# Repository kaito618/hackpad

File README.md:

# my own macropad (kpad)
### 3x3 macropad with an oled screen

this project is a macropad i designed to fill my needs using my pc what it has :

- 3x3 MX switches (programmable)
- oled screen
- 3d case (optional)
- firmaware

## the schematics

- using the xiao rp2040 as our microcontroller
- connecting the switches directly using "single pin method"
- using i2c with the oled screen 

## PCB design 

## 3d case 

bom
-
| Reference | Component | Footprint | Qty | Description | price | link |
|---|---|---|---|---|---|---|
| U1 | Seeed XIAO RP2040 | XIAO-RP2040-DIP | 1 | Main Microcontroller (MCU) | 
| SW1-SW9 | MX Switches | SW_Cherry_MX_1.00u_PCB | 9 | 1.00u Mechanical switches |
| J1 | 0.91" OLED Display | PinHeader_1x04_P2.54mm | 1 | 128x32 I2C OLED Screen |
| J2 | pcb | pcb | 1 | the board (alr bought) |
| J3 | 3d case | case | 1 | the case (alr bought) |

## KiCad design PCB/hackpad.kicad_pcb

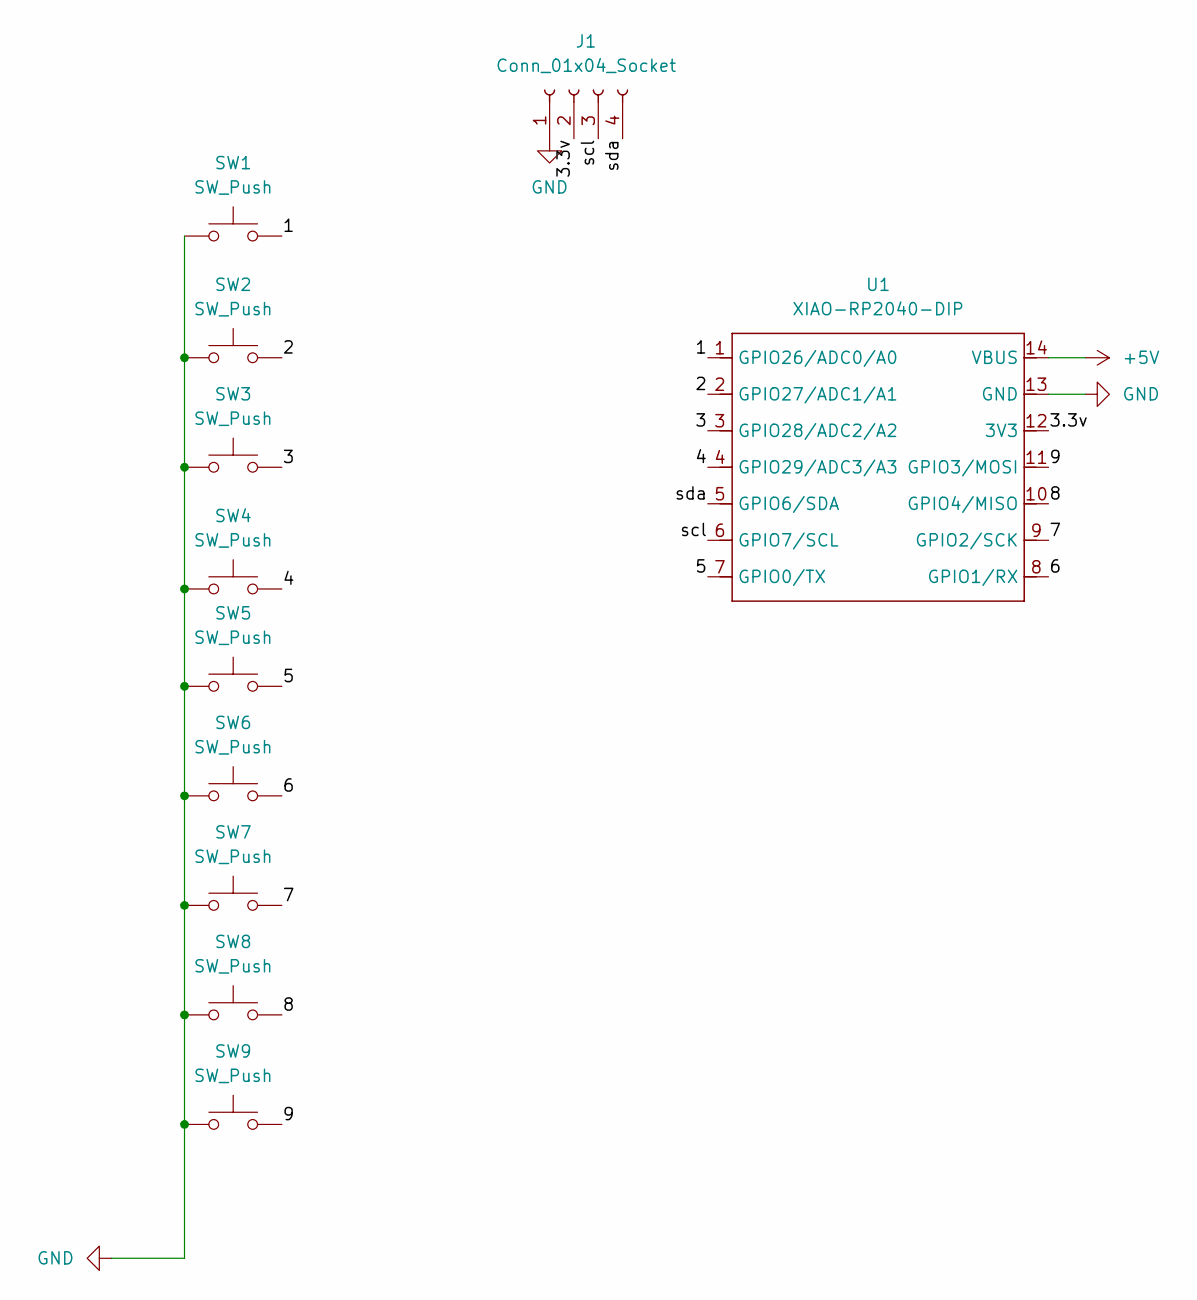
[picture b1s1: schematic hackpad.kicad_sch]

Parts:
J1: Conn_01x04_Socket; PinHeader_1x04_P2.54mm_Vertical
SW1, SW2, SW3, SW4, SW5, SW6, SW7, SW8, SW9: SW_Push; SW_Cherry_MX_1.00u_PCB
U1: XIAO-RP2040-DIP

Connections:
+5V: U1.14 (VBUS)
/1: SW1.2, U1.1 (GPIO26/ADC0/A0)
/2: SW2.2, U1.2 (GPIO27/ADC1/A1)
/3: SW3.2, U1.3 (GPIO28/ADC2/A2)
/3.3v: J1.2, U1.12 (3V3)
/4: SW4.2, U1.4 (GPIO29/ADC3/A3)
/5: SW5.2, U1.7 (GPIO0/TX)
/6: SW6.2, U1.8 (GPIO1/RX)
/7: SW7.2, U1.9 (GPIO2/SCK)
/8: SW8.2, U1.10 (GPIO4/MISO)
/9: SW9.2, U1.11 (GPIO3/MOSI)
/scl: J1.3, U1.6 (GPIO7/SCL)
/sda: J1.4, U1.5 (GPIO6/SDA)
GND: J1.1, SW1.1, SW2.1, SW3.1, SW4.1, SW5.1, SW6.1, SW7.1, SW8.1, SW9.1, U1.13 (GND)

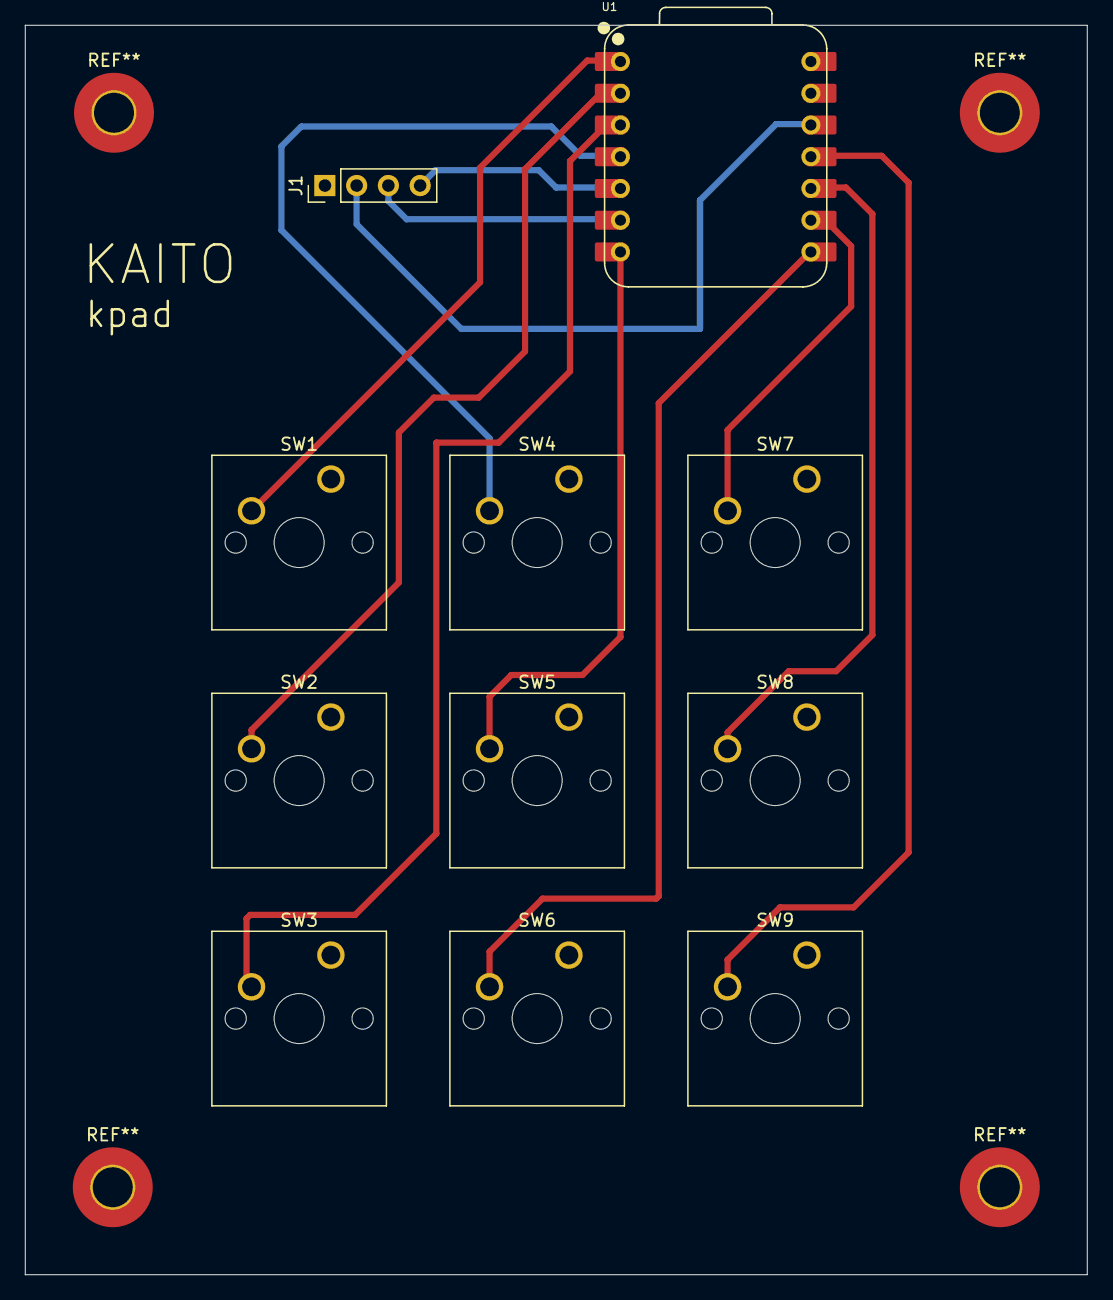
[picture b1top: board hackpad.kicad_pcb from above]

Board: 2 copper layers, 85.0 x 100.0 mm, 11 parts (0 on the bottom side), 13 nets.

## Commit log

2026-01-05 Create s
2026-01-05 Update s
2026-05-01 polished readme
    Updated project description, added schematics, and BOM.
